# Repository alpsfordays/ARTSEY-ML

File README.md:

# ARTSEY-ML
An ARTSEY Paintbrush for ML

This is a PCB for using [ARTSEY](https://artsey.io) with Cherry ML. It's designed for 18mm CHerry ML spacing - Plum keycaps will not fit on this.
It uses a [nice!nano](https://nicekeyboards.com/nice-nano) or Pro Micro, and is compatible with the Paintbrush's firmware on ZMK/QMK for both.

I provide no guarantees for this project; I've assembled and tested both, and the left-hand board running ZMK travels with me. Assembly is fairly straightforward: solder the SMD switch and reset button first, the the sockets/headers and finally the ML switches and controller, component side up. There is a left board and a right board; however, if you don't plan on making it Bluetooth and can forego the SMD reset and power switch, the boards are fully reversible by flipping the PCB and installing the controller component side down - use the firmware you'd use normally (if it's a left-hand board, use the left-hand firmware and vice versa).

All my hardware designs are licensed under the [Creative Commons
Attribution-NonCommercial-ShareAlike 4.0](https://creativecommons.org/licenses/by-nc-sa/4.0/)
license.

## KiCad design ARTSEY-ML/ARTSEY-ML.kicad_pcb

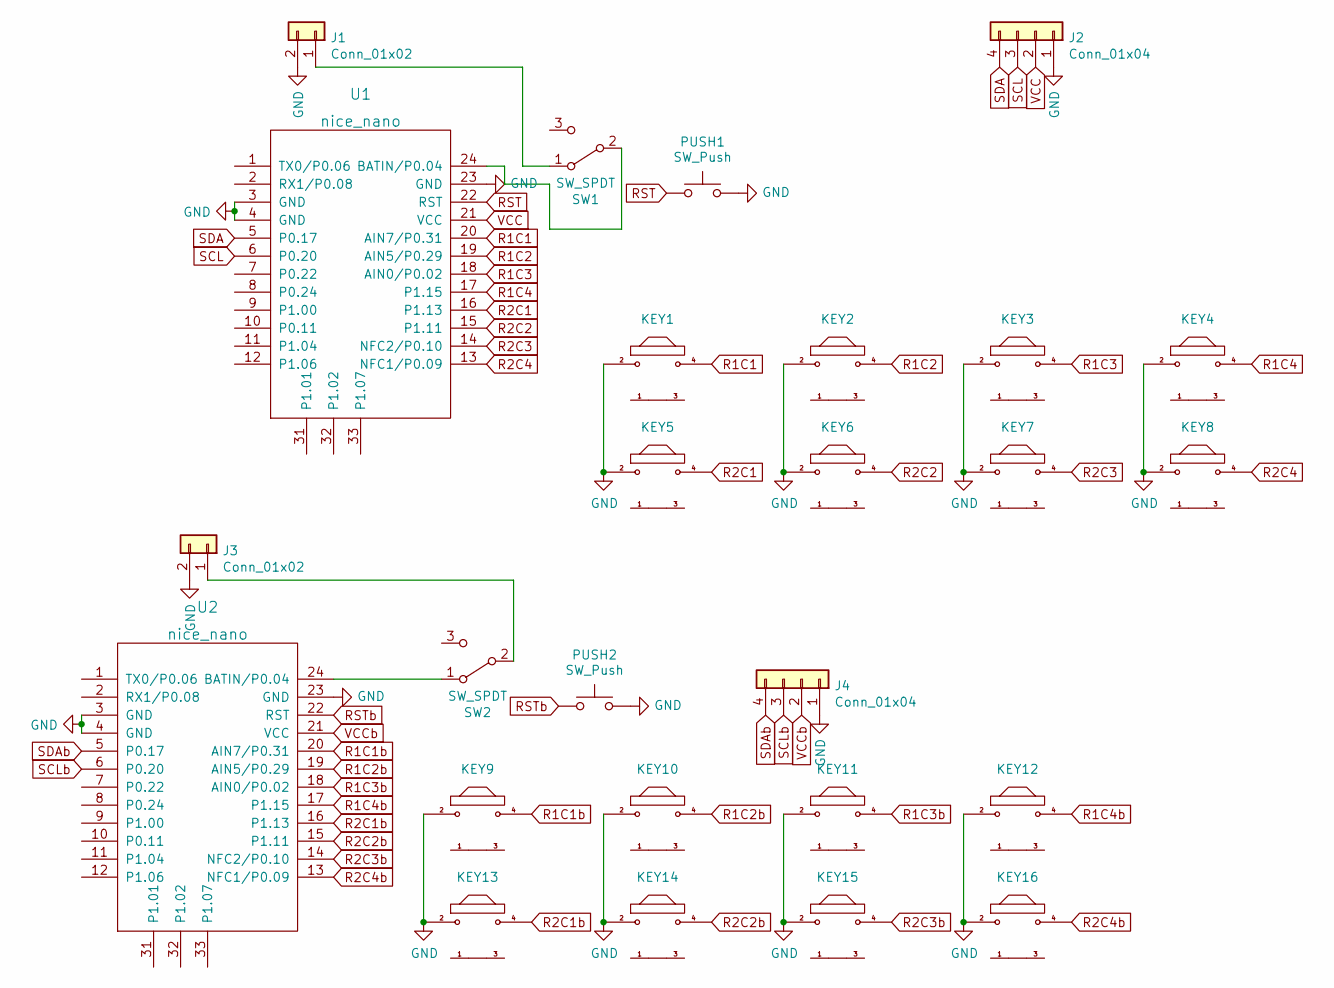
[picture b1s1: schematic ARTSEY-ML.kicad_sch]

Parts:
J1, J3: Conn_01x02; PinHeader_1x02_P2.54mm_Vertical
J2, J4: Conn_01x04; OLED
KEY1, KEY2, KEY3, KEY4, KEY5, KEY6, KEY7, KEY8, KEY9, KEY10, KEY11, KEY12, KEY13, KEY14, KEY15, KEY16: ML; NoSilk_SW_Cherry_ML_1u_Centred
PUSH1, PUSH2: SW_Push; SW_SPST_B3U-1000P
SW1, SW2: SW_SPDT; SW_SPDT_PCM12
U1, U2: nice_nano

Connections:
GND: J1.2, J2.1, J3.2, J4.1, KEY1.2, KEY2.2, KEY3.2, KEY4.2, KEY5.2, KEY6.2, KEY7.2, KEY8.2, KEY9.2, KEY10.2, KEY11.2, KEY12.2, KEY13.2, KEY14.2, KEY15.2, KEY16.2, PUSH1.2, PUSH2.2, U1.3 (GND), U1.4 (GND), U1.23 (GND), U2.3 (GND), U2.4 (GND), U2.23 (GND)
unnamed: J1.1, SW1.1 (A)
unnamed: J3.1, SW2.2 (B)
unnamed: SW1.2 (B), U1.24 (BATIN/P0.04)
unnamed: SW2.1 (A), U2.24 (BATIN/P0.04)
R1C1: KEY1.4, U1.20 (AIN7/P0.31)
R1C1b: KEY9.4, U2.20 (AIN7/P0.31)
R1C2: KEY2.4, U1.19 (AIN5/P0.29)
R1C2b: KEY10.4, U2.19 (AIN5/P0.29)
R1C3: KEY3.4, U1.18 (AIN0/P0.02)
R1C3b: KEY11.4, U2.18 (AIN0/P0.02)
R1C4: KEY4.4, U1.17 (P1.15)
R1C4b: KEY12.4, U2.17 (P1.15)
R2C1: KEY5.4, U1.16 (P1.13)
R2C1b: KEY13.4, U2.16 (P1.13)
R2C2: KEY6.4, U1.15 (P1.11)
R2C2b: KEY14.4, U2.15 (P1.11)
R2C3: KEY7.4, U1.14 (NFC2/P0.10)
R2C3b: KEY15.4, U2.14 (NFC2/P0.10)
R2C4: KEY8.4, U1.13 (NFC1/P0.09)
R2C4b: KEY16.4, U2.13 (NFC1/P0.09)
RST: PUSH1.1, U1.22 (RST)
RSTb: PUSH2.1, U2.22 (RST)
SCL: J2.3, U1.6 (P0.20)
SCLb: J4.3, U2.6 (P0.20)
SDA: J2.4, U1.5 (P0.17)
SDAb: J4.4, U2.5 (P0.17)
VCC: J2.2, U1.21 (VCC)
VCCb: J4.2, U2.21 (VCC)

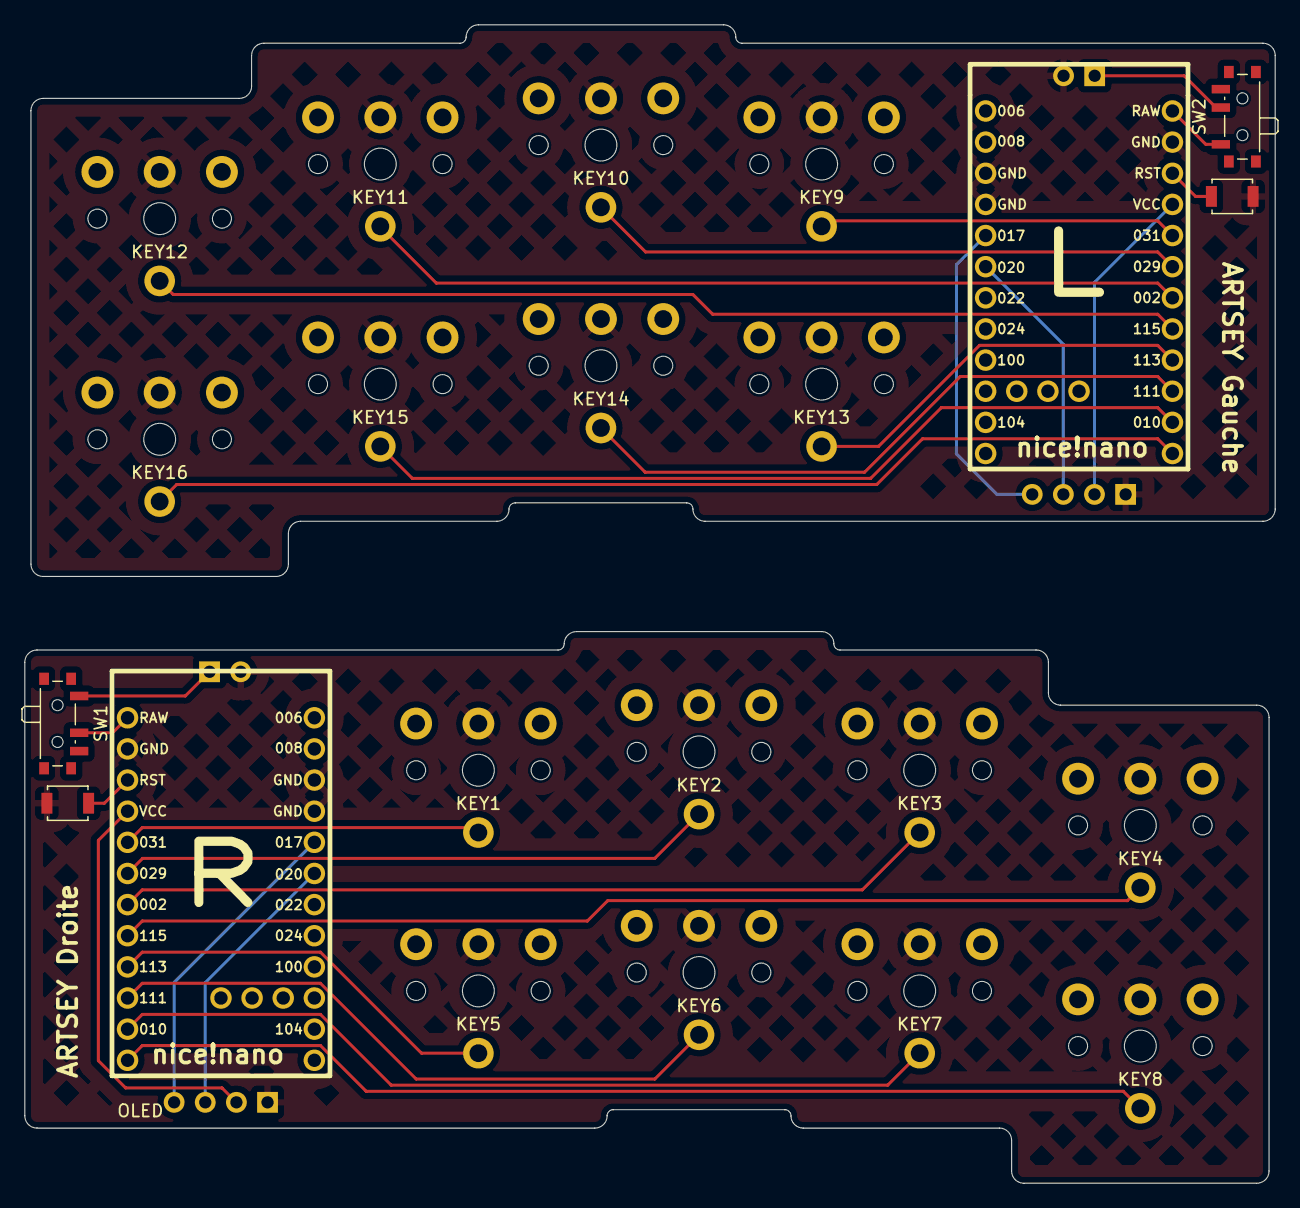
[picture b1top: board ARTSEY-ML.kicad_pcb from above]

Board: 2 copper layers, 102.0 x 94.5 mm, 26 parts (1 on the bottom side), 29 nets.
